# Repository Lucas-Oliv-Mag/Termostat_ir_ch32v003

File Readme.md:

# 🌡️ IR Thermostat — CH32V003

A portable, compact, low-power infrared thermometer based on the **CH32V003** microcontroller, featuring contactless temperature reading via the **MLX90614** sensor and an **I²C OLED SSD1306** display.

Built with **100% custom firmware** — HAL and sensor libraries written from scratch, with no dependency on third-party frameworks.

---

## ✨ Features

- 📡 Contactless infrared temperature reading via **MLX90614**
- 🖥️ **128x64 SSD1306 OLED** display over I²C
- 🔘 Single tactile button to trigger a reading
- 🌗 **Automatic brightness control** via a 5mm LDR (adjusts to ambient light)
- 🔋 **250mAh LiPo battery (503020)** for portable use
- ⚡ Charging via **TP4056** with integrated battery protection (0.5C)
- 🔌 3-pin header (5V / GND / SWIO) for external power and programming

---

## 🧩 Hardware

| Component | Description |
|---|---|
| **MCU** | CH32V003 (RISC-V, low cost, low power) |
| **Temperature sensor** | MLX90614 (IR, I²C) |
| **Display** | SSD1306 OLED 128x64, I²C |
| **Light sensor** | 5mm LDR (automatic brightness control) |
| **Input** | 1x tactile button (start/reading) |
| **Power source** | 250mAh LiPo battery, 503020 |
| **Charger** | TP4056 with battery protection (over-charge/discharge/current) |
| **Charge rate** | 0.5C (~125mA) |
| **External connector** | 3-pin header — 5V, GND, SWIO |

---

## ⚠️ Important warnings

> **Read carefully before using or programming the device.**

### 🚫 Never flash the MCU while pressing the button
The **SWIO** pin (used for programming/debugging) shares the same **I/O line** as the tactile button. Pressing the button during flashing can cause a **bus conflict**, flashing failure, or undefined MCU behavior.

### 🚫 Never connect USB while powering via the external 5V header
The **TP4056** charger and the 3-pin header **have no isolation between power sources**. Powering the circuit simultaneously through **USB** and the **external header (5V)** can cause:
- Short circuit between power sources
- Unwanted reverse current
- Damage to the TP4056, the battery, or the MCU

**Use only one power source at a time.**

---

## 🌡️ Operating conditions

- **Maximum recommended ambient temperature:** ~40 °C
- Above this limit, the MLX90614 sensor accuracy and the LiPo battery lifespan may be affected.

---

## 🔋 Battery and charging

| Parameter | Value |
|---|---|
| Capacity | 250 mAh |
| Model | 503020 (LiPo) |
| Charge rate | 0.5C (~125 mA) |
| Charge controller | TP4056 |
| Protection | Over-charge, over-discharge, and over-current |

---

## 💻 Firmware

The firmware is **built entirely from scratch**, without relying on any third-party HAL (such as the official WCH HAL), including:

- **Custom HAL** for GPIO, I²C, ADC, and timing on the CH32V003
- **Custom library** for MLX90614 communication
- **Custom library** for SSD1306 display control
- LDR reading routine with a brightness adjustment curve (PWM/lookup table)
- Simple state machine: `standby → reading → display → standby`

### repository structure

```
/firmware
  /*COMING SOON*
/hardware
  /schematics
  /pcb
  /datasheets
/docs
README.md
LICENSE
```

---

## 🚀 Usage

1. Power the device via battery (or the external 5V header, **never both at the same time**).
2. Press the tactile button to start a temperature reading.
3. The temperature will be shown on the OLED display.
4. The display brightness adjusts automatically based on the ambient light detected by the LDR.

---

## 🛠️ Flashing

1. Connect the programmer (WCH-Link or compatible) to the 3-pin header (**5V / GND / SWIO**).
2. **Make sure the tactile button is not being pressed.**
3. Flash normally using your preferred tool (e.g., `wchisp`, MounRiver, OpenOCD with RISC-V support).

---

## 🤝 Contributing

Suggestions, fixes, and improvements are welcome via issues or pull requests.

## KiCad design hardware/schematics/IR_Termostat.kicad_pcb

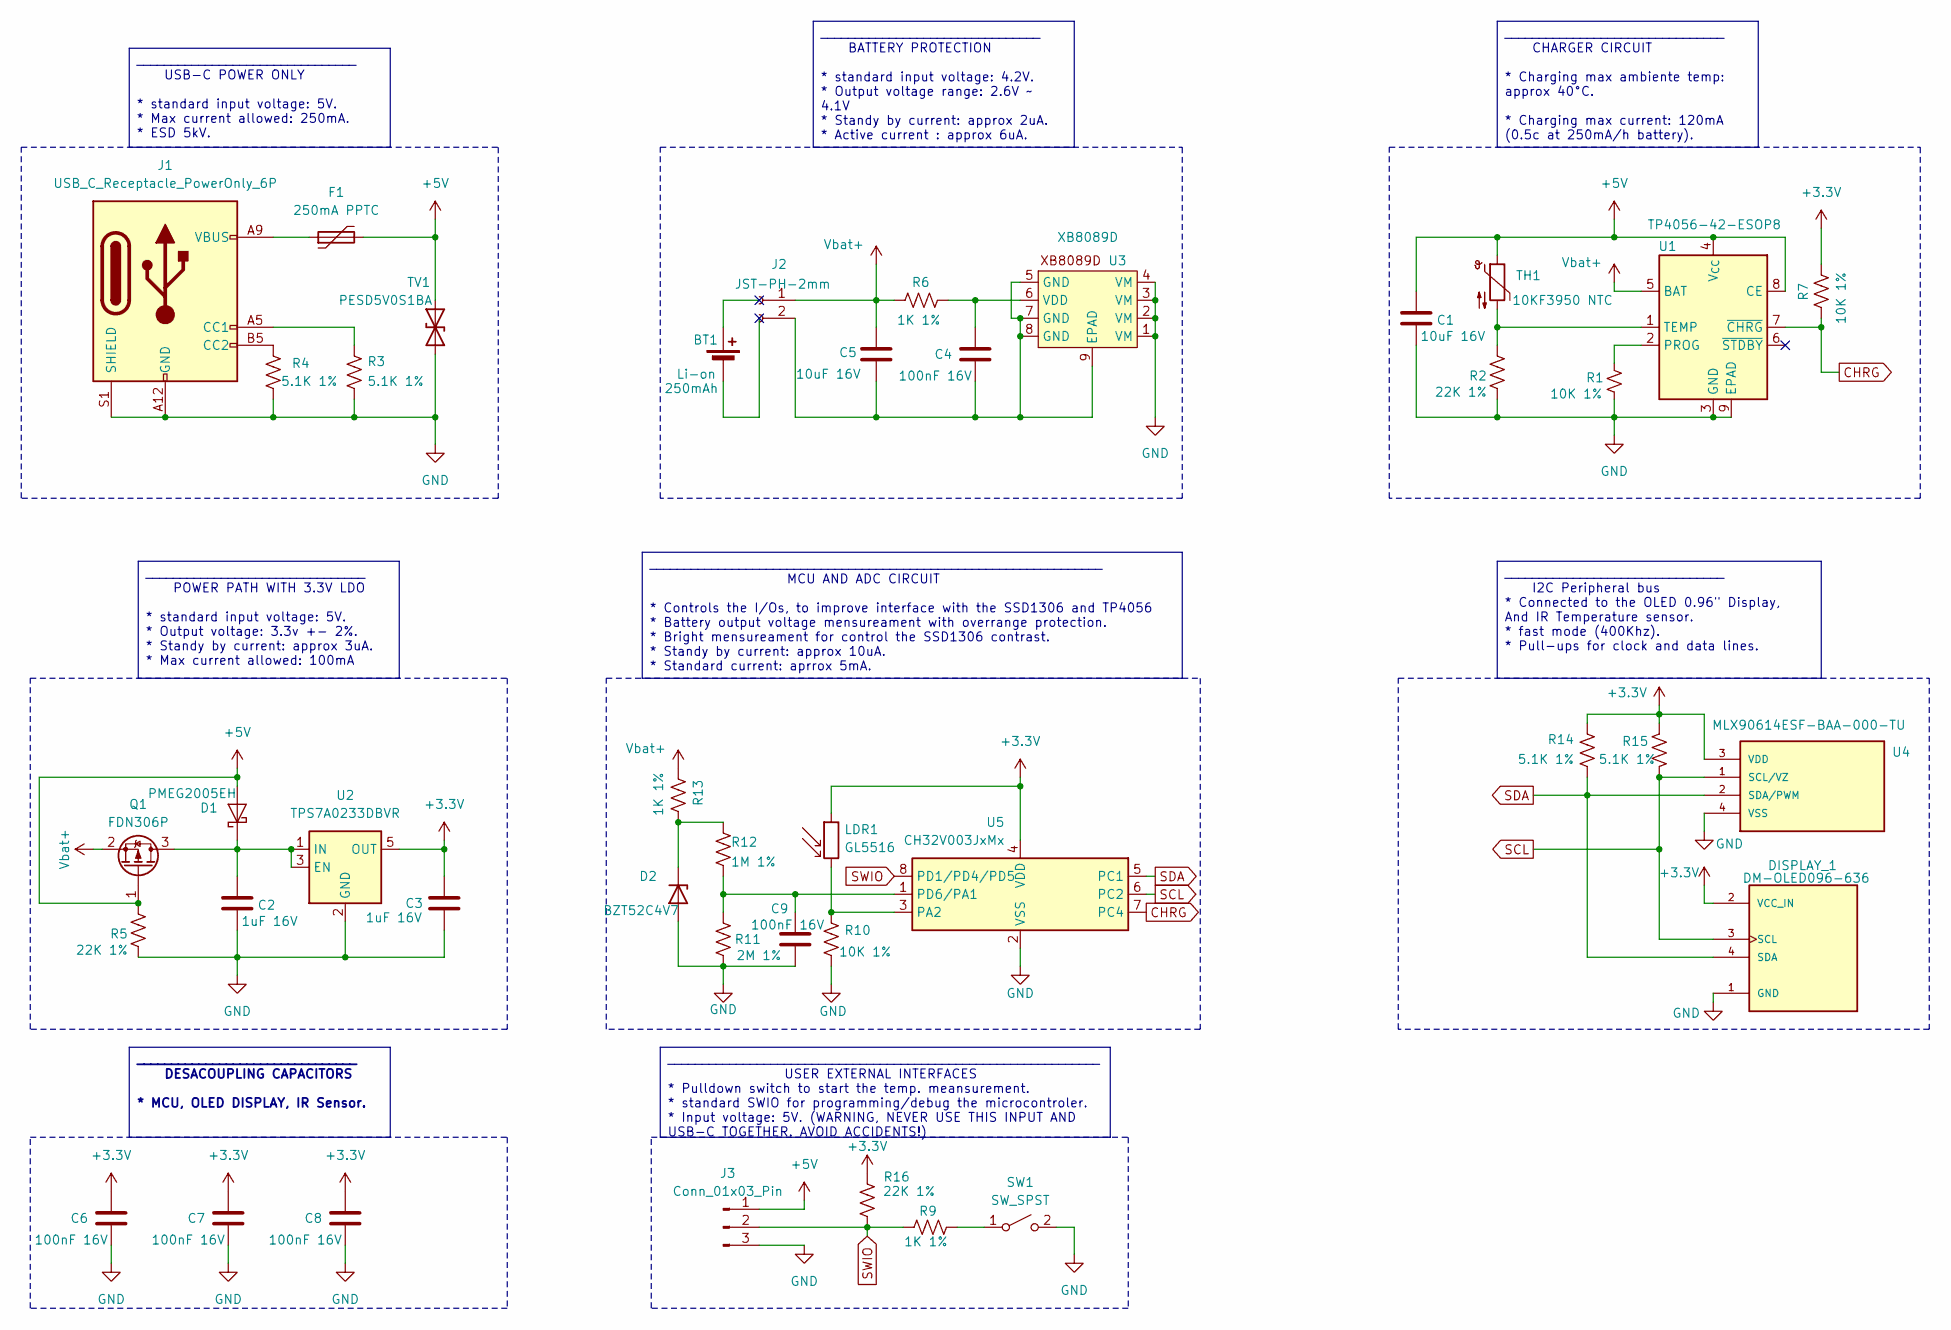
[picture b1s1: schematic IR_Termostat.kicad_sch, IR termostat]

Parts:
BT1: 250mAh
C1, C5: 10uF 16V; C_0805_2012Metric_Pad1.18x1.45mm_HandSolder
C2, C3: 1uF 16V; C_0805_2012Metric_Pad1.18x1.45mm_HandSolder
C4, C6, C7, C8, C9: 100nF 16V; C_0805_2012Metric_Pad1.18x1.45mm_HandSolder
D1: PMEG2005EH; D_SOD-123F
D2: BZT52C4V7; D_SOD-123F
DISPLAY_1: DM-OLED096-636; MODULE_DM-OLED096-636; PARTREV 2018-09-10
F1: 250mA PPTC; R_1206_3216Metric_Pad1.30x1.75mm_HandSolder
J1: USB_C_Receptacle_PowerOnly_6P; USB_C_Receptacle_GCT_USB4125-xx-x_6P_TopMnt_Horizontal
J2: JST-PH-2mm; JST_PH_S2B-PH-K_1x02_P2.00mm_Horizontal
J3: Conn_01x03_Pin; PinHeader_1x03_P2.54mm_Vertical
LDR1: GL5516; R_LDR_5.1x4.3mm_P3.4mm_Vertical
Q1: FDN306P; SOT-23
R1, R7, R10: 10K 1%; R_0805_2012Metric_Pad1.20x1.40mm_HandSolder
R2, R5, R16: 22K 1%; R_0805_2012Metric_Pad1.20x1.40mm_HandSolder
R3, R4, R14, R15: 5.1K 1%; R_0805_2012Metric_Pad1.20x1.40mm_HandSolder
R6, R9, R13: 1K 1%; R_0805_2012Metric_Pad1.20x1.40mm_HandSolder
R11: 2M 1%; R_0805_2012Metric_Pad1.20x1.40mm_HandSolder
R12: 1M 1%; R_0805_2012Metric_Pad1.20x1.40mm_HandSolder
SW1: SW_SPST; SW_PUSH_6mm
TH1: 10KF3950 NTC; R_0805_2012Metric_Pad1.20x1.40mm_HandSolder
TV1: PESD5V0S1BA; D_SOD-323_HandSoldering
U1: TP4056-42-ESOP8; SOIC-8-1EP_3.9x4.9mm_P1.27mm_EP2.41x3.3mm_ThermalVias
U2: TPS7A0233DBVR; SOT-23-5
U3: XB8089D; SOIC-8-1EP_3.9x4.9mm_P1.27mm_EP2.29x3mm_ThermalVias
U4: MLX90614ESF-BAA-000-TU; TO254P942H425-4; PARTREV 13
U5: CH32V003JxMx; SOP-8_3.9x4.9mm_P1.27mm

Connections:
+3.3V: C3.1, C6.1, C7.1, C8.1, DISPLAY_1.2 (VCC_IN), LDR1.1, R7.2, R14.2, R15.2, R16.2, U2.5 (OUT), U4.3 (VDD), U5.4 (VDD)
+5V: C1.1, D1.2 (A), F1.2, J3.1, Q1.1 (G), R5.1, TH1.1, TV1.2 (A2), U1.4 (V_{CC}), U1.8 (CE)
CHRG: R7.1, U1.7 (~CHRG), U5.7 (PC4)
GND: C1.2, C2.2, C3.2, C6.2, C7.2, C8.2, C9.2, D2.2 (A), DISPLAY_1.1 (GND), J1.A12 (GND), J1.B12 (GND), J1.S1 (SHIELD), J3.3, R1.2, R2.2, R3.2, R4.2, R5.2, R10.2, R11.2, SW1.2 (B), TV1.1 (A1), U1.3 (GND), U1.9 (EPAD), U2.2 (GND), U3.1 (VM), U3.2 (VM), U3.3 (VM), U3.4 (VM), U4.4 (VSS), U5.2 (VSS)
unnamed: C2.1, D1.1 (K), Q1.3 (D), U2.1 (IN), U2.3 (EN)
unnamed: D2.1 (K), R12.1, R13.1
unnamed: F1.1, J1.A9 (VBUS), J1.B9 (VBUS)
unnamed: J1.A5 (CC1), R3.1
unnamed: J1.B5 (CC2), R4.1
unnamed: C4.2, C5.2, J2.2, U3.5 (GND), U3.7 (GND), U3.8 (GND), U3.9 (EPAD)
unnamed: R9.2, SW1.1 (A)
unnamed: R1.1, U1.2 (PROG)
unnamed: R2.1, TH1.2, U1.1 (TEMP)
unnamed: C4.1, R6.2, U3.6 (VDD)
unnamed: LDR1.2, R10.1, U5.3 (PA2)
unnamed: C9.1, R11.1, R12.2, U5.1 (PD6/PA1)
SCL: DISPLAY_1.3 (SCL), R15.1, U4.1 (SCL/VZ), U5.6 (PC2)
SDA: DISPLAY_1.4 (SDA), R14.1, U4.2 (SDA/PWM), U5.5 (PC1)
SWIO: J3.2, R9.1, R16.1, U5.8 (PD1/PD4/PD5)
Vbat+: C5.1, J2.1, Q1.2 (S), R6.1, R13.2, U1.5 (BAT)

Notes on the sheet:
__________________________________________________________________ MCU AND ADC CIRCUIT * Controls the I/Os, to improve interface with the SSD1306 and TP4056 * Battery output voltage mensureament with overrange protection. * Bright mensureament for control the SSD1306 contrast. * Standy by current: 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
________________________________ I2C Peripheral bus * Connected to the OLED 0.96" Display, And IR Temperature sensor. * fast mode (400Khz). * Pull-ups for clock and data lines.
________________________________ DESACOUPLING CAPACITORS * MCU, OLED DISPLAY, IR Sensor.
________________________________ POWER PATH WITH 3.3V LDO * standard input voltage: 5V. * Output voltage: 3.3v +- 2%. * Standy by current: approx 3uA. * Max current allowed: 100mA
_______________________________________________________________ USER EXTERNAL INTERFACES * Pulldown switch to start the temp. meansurement. * standard SWIO for programming/debug the microcontroler. * Input voltage: 5V. (WARNING, NEVER USE THIS INPUT AND USB-C TOGETHER. AVOID ACCIDENTS!)
________________________________ CHARGER CIRCUIT * Charging max ambiente temp: approx 40°C. * Charging max current: 120mA (0.5c at 250mA/h battery).
________________________________ USB-C POWER ONLY * standard input voltage: 5V. * Max current allowed: 250mA. * ESD 5kV.
________________________________ BATTERY PROTECTION * standard input voltage: 4.2V. * Output voltage range: 2.6V ~ 4.1V * Standy by current: approx 2uA. * Active current : approx 6uA.

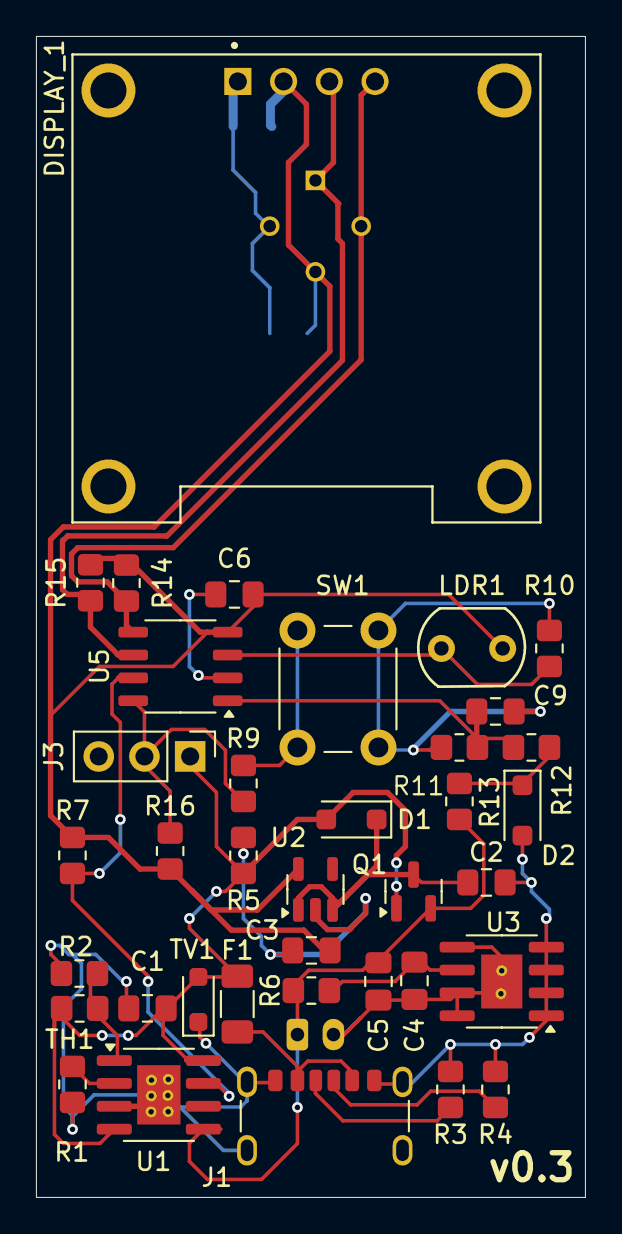
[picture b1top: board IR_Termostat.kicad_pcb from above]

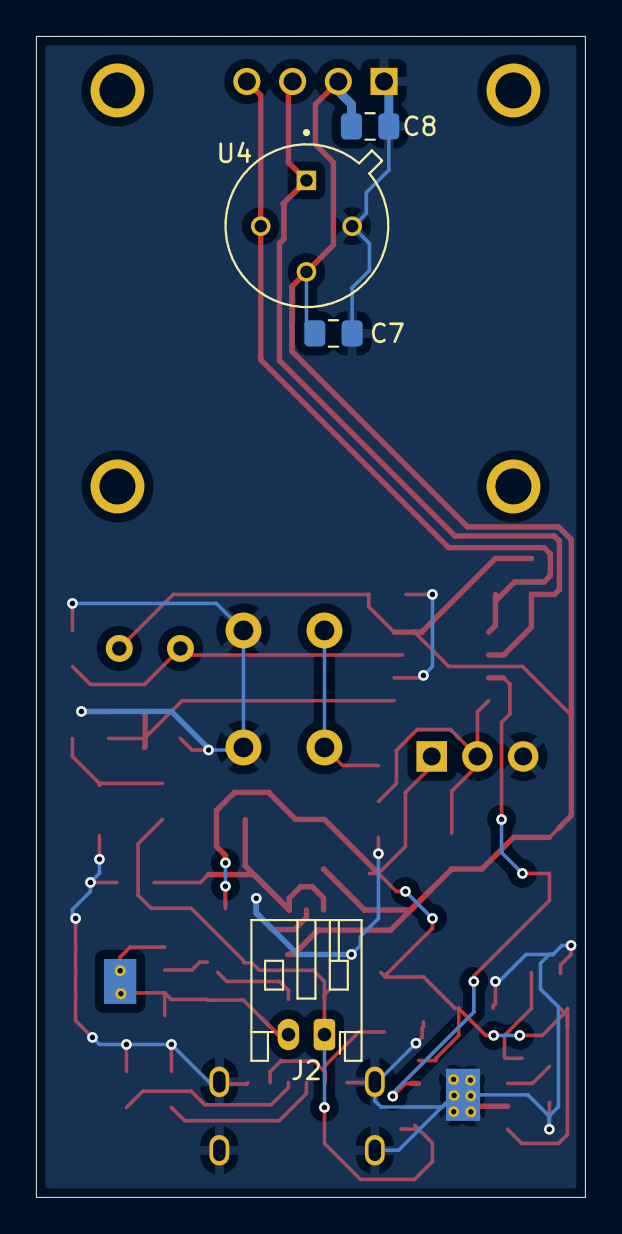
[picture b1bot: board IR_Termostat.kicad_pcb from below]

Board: 2 copper layers, 30.5 x 64.5 mm, 41 parts (4 on the bottom side), 20 nets.

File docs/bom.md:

| **#**  | Id | Designador    | Footprint                                              | Quantidade | Designação                    | Fornecedor e referência |   |   |
|--------|----|---------------|--------------------------------------------------------|------------|-------------------------------|-------------------------|---|---|
| **1**  | 1  | Q1            | SOT-23                                                 | 1          | FDN306P                       |                         |   |   |
| **2**  | 2  | R5,R2,R11,R16 | R_0805_2012Metric_Pad1.20x1.40mm_HandSolder            | 4          | 22K 1%                        |                         |   |   |
| **3**  | 3  | R6,R13,R9     | R_0805_2012Metric_Pad1.20x1.40mm_HandSolder            | 3          | 1K 1%                         |                         |   |   |
| **4**  | 4  | D2            | D_SOD-123F                                             | 1          | BZT52C4V7                     |                         |   |   |
| **5**  | 5  | TV1           | D_SOD-323_HandSoldering                                | 1          | PESD5V0S1BA                   |                         |   |   |
| **6**  | 6  | D1            | D_SMA_Handsoldering                                    | 1          | SSL14                         |                         |   |   |
| **7**  | 7  | F1            | R_1206_3216Metric_Pad1.30x1.75mm_HandSolder            | 1          | 250mA PPTC                    |                         |   |   |
| **8**  | 8  | C5,C1         | C_0805_2012Metric_Pad1.18x1.45mm_HandSolder            | 2          | 10uF 16V                      |                         |   |   |
| **9**  | 9  | R4,R3,R14,R15 | R_0805_2012Metric_Pad1.20x1.40mm_HandSolder            | 4          | 5.1K 1%                       |                         |   |   |
| **10** | 10 | C2,C3         | C_0805_2012Metric_Pad1.18x1.45mm_HandSolder            | 2          | 1uF 16V                       |                         |   |   |
| **11** | 11 | U1            | SOIC-8-1EP_3.9x4.9mm_P1.27mm_EP2.41x3.3mm_ThermalVias  | 1          | TP4056-42-ESOP8               |                         |   |   |
| **12** | 12 | SW1           | SW_PUSH_6mm                                            | 1          | SW_SPST                       |                         |   |   |
| **13** | 13 | C4,C6,C7,C8   | C_0805_2012Metric_Pad1.18x1.45mm_HandSolder            | 4          | 100nF 16V                     |                         |   |   |
| **14** | 14 | U3            | SOIC-8-1EP_3.9x4.9mm_P1.27mm_EP2.29x3mm_ThermalVias    | 1          | ~                             |                         |   |   |
| **15** | 15 | U2            | SOT-23-3                                               | 1          | XC6206P-3.3V                  |                         |   |   |
| **16** | 16 | J3            | PinHeader_1x03_P2.54mm_Vertical                        | 1          | Conn_01x03_Pin                |                         |   |   |
| **17** | 17 | LDR1          | R_LDR_5.1x4.3mm_P3.4mm_Vertical                        | 1          | GL5516                        |                         |   |   |
| **18** | 18 | DISPLAY_1     | MODULE_DM-OLED096-636                                  | 1          | DM-OLED096-636                |                         |   |   |
| **19** | 19 | R10,R1,R7     | R_0805_2012Metric_Pad1.20x1.40mm_HandSolder            | 3          | 10K 1%                        |                         |   |   |
| **20** | 20 | U5            | SOP-8_3.9x4.9mm_P1.27mm                                | 1          | CH32V003JxMx                  |                         |   |   |
| **21** | 21 | TH1           | R_0805_2012Metric_Pad1.20x1.40mm_HandSolder            | 1          | 10KF3950 NTC                  |                         |   |   |
| **22** | 22 | R12           | R_0805_2012Metric_Pad1.20x1.40mm_HandSolder            | 1          | 9.1K 1%                       |                         |   |   |
| **23** | 23 | J1            | USB_C_Receptacle_GCT_USB4125-xx-x_6P_TopMnt_Horizontal | 1          | USB_C_Receptacle_PowerOnly_6P |                         |   |   |
| **24** | 24 | J2            | JST_PH_S2B-PH-K_1x02_P2.00mm_Horizontal                | 1          | JST-PH-2mm                    |                         |   |   |
| **25** | 25 | U4            | TO254P942H425-4                                        | 1          | MLX90614ESF-BAA-000-TU        |                         |   |   |

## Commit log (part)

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2026-06-25 Initial commit
    Hardware project start
2026-06-25 Feat: NTC improved
    Also added CC1 and CC2 Resistors and a text box explaining the eletrical tolerances
2026-06-25 Style: Schematic refactored by sectors
2026-06-26 Feat: Power path with LDO implemented
    Using high efficiency componentes to minimize the voltage drop-out and heat sink, for allowed levels
2026-06-26 feat: Battery protection circuit implemented
    Added a protection resiable IC for: Over and Under charge, short, inverse polarity
2026-06-26 feat: pullup resistor to charge IC I/Os
    Also redesingned the sch. for better visual
2026-06-27 Fix: Switched Pullup resistors source from TP4056
    Before, the resistors responsable for the pullup of the CHRGD and STDBY pins from the charger IC are connect on 5V line, now they are on 3.3V power supply from LDO.
2026-06-27 Feat: main MCU and ADC
    Included the CH32V003J4M6, also bring up a voltage divider with overrange protection to read the battery voltage with realible, and brightness mensurement with another ADC channel.
2026-06-28 feat: External interface improviment.
    Included a header pin por programming/debuging the embedded, also added decoupling capacitors and a touch switch for make interface with the MCU
2026-06-28 Feat: Added I2C Bus peripherals
2026-06-30 Fix: I2C Peripheral bus footprint and symbol
2026-06-30 Fix: power path mosfet footprint
    The footprint of the power path mosfet now it's pin-to-pin with the skemathic.
